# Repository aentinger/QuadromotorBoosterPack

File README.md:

💾 Quadromotor BoosterPack
==========================

# 📸 Image

# 📂 Description

The Quadromotor BoosterPack in combination with a MSP430 Launchpad facilitates the control of a 1, 2 or 4 DC motors, or alternatively  of 2 stepper motors. Additionally, outputs of the motor drivers can be connected in parallel. Therefor, two motors with an maximum output current of 2 A can be controlled, or one motor with an maximum output current of 4 A. For a quick and easy start a sample Code Composer Studio project (written in programming language C) is available.

**Features**

* Control of 1, 2 or 4 DC motors OR 
* Control of 2 stepper motors
* Speed and rotational direction adjustable
* Supply voltage range: 4 V to 16 V
* Output current per motor for 4/2/1 motors: 1 A / 2 A / 4 A
* To be used with MSP430 Launchpad
* Sample projects available for Code Composer Studio

# 🎥 [Video](images/quadromotor_booster_pack_demo.mp4)

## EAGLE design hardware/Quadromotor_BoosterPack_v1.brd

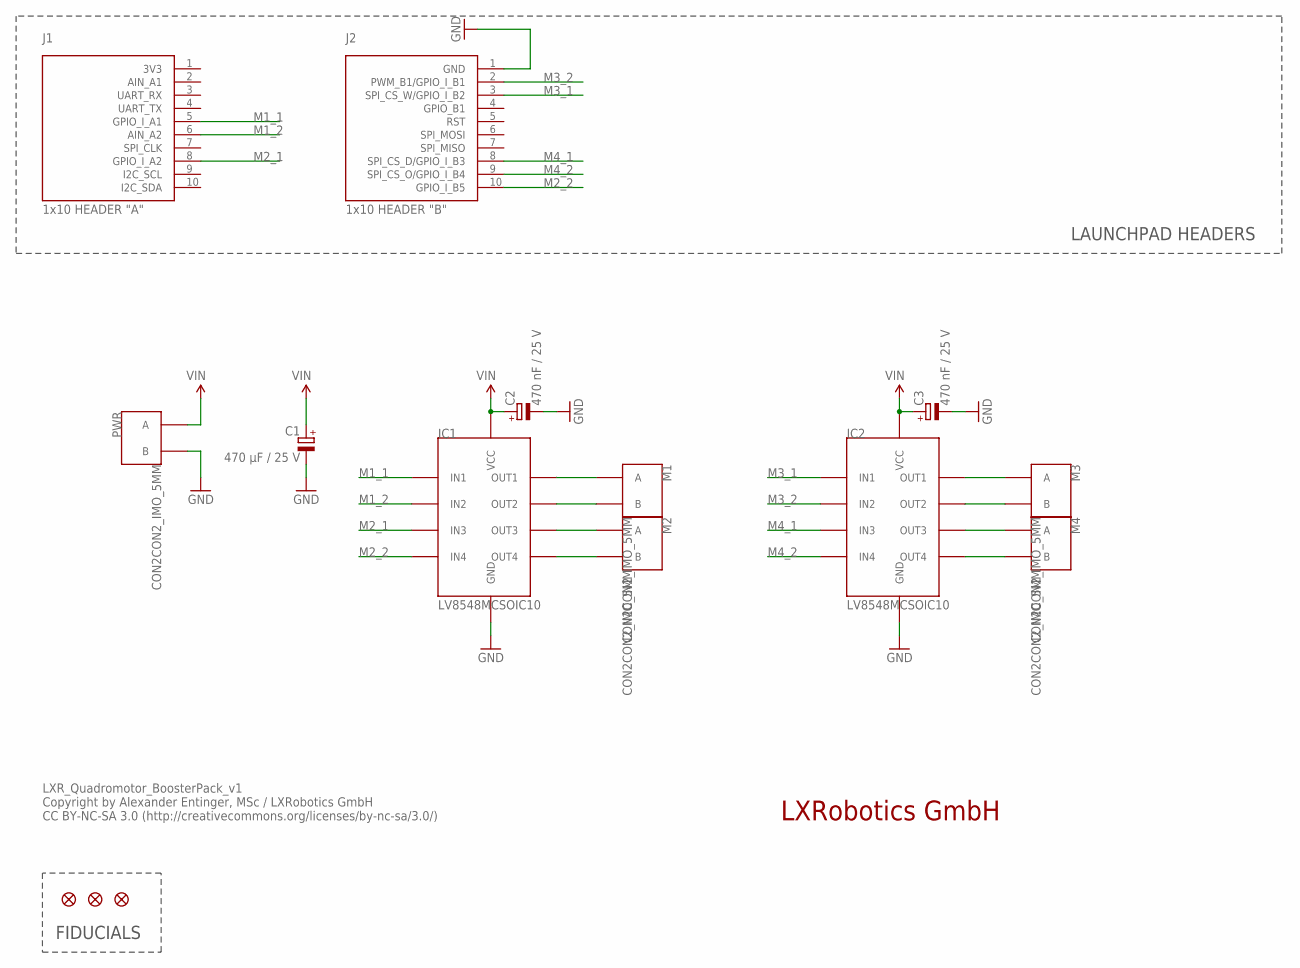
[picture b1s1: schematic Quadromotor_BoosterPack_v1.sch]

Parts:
C1: 470 µF / 25 V; E5-10,5
C2, C3: 470 nF / 25 V; KEMET_A
FID1, FID2, FID3: FIDUCIAL; FIDUCIAL_L10
IC1, IC2: LV8548MCSOIC10; SOIC10
J1: 1x10 HEADER "A"; 1X10
J2: 1x10 HEADER "B"; 1X10
M1, M2, M3, M4: CON2CON2_IMO_5MM; CON2_IMO
PWR: CON2CON2_IMO_5MM; CON2_IMO

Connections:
GND: C1.-, C2.CATHODE (-), C3.CATHODE (-), IC1.6 (GND), IC2.6 (GND), J2.1 (GND), PWR.P$2 (B)
M1_1: IC1.2 (IN1), J1.5 (GPIO_I_A1)
M1_2: IC1.3 (IN2), J1.6 (AIN_A2)
M2_1: IC1.4 (IN3), J1.8 (GPIO_I_A2)
M2_2: IC1.5 (IN4), J2.10 (GPIO_I_B5)
M3_1: IC2.2 (IN1), J2.3 (SPI_CS_W/GPIO_I_B2)
M3_2: IC2.3 (IN2), J2.2 (PWM_B1/GPIO_I_B1)
M4_1: IC2.4 (IN3), J2.8 (SPI_CS_D/GPIO_I_B3)
M4_2: IC2.5 (IN4), J2.9 (SPI_CS_O/GPIO_I_B4)
unnamed: IC1.10 (OUT1), M1.P$1 (A)
unnamed: IC1.9 (OUT2), M1.P$2 (B)
unnamed: IC1.8 (OUT3), M2.P$1 (A)
unnamed: IC1.7 (OUT4), M2.P$2 (B)
unnamed: IC2.10 (OUT1), M3.P$1 (A)
unnamed: IC2.9 (OUT2), M3.P$2 (B)
unnamed: IC2.8 (OUT3), M4.P$1 (A)
unnamed: IC2.7 (OUT4), M4.P$2 (B)
VIN: C1.+, C2.ANODE (+), C3.ANODE (+), IC1.1 (VCC), IC2.1 (VCC), PWR.P$1 (A)

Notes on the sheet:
LAUNCHPAD HEADERS
FIDUCIALS
LXRobotics GmbH
LXR_Quadromotor_BoosterPack_v1 Copyright by Alexander Entinger, MSc / LXRobotics GmbH CC BY-NC-SA 3.0 (http://creativecommons.org/licenses/by-nc-sa/3.0/)

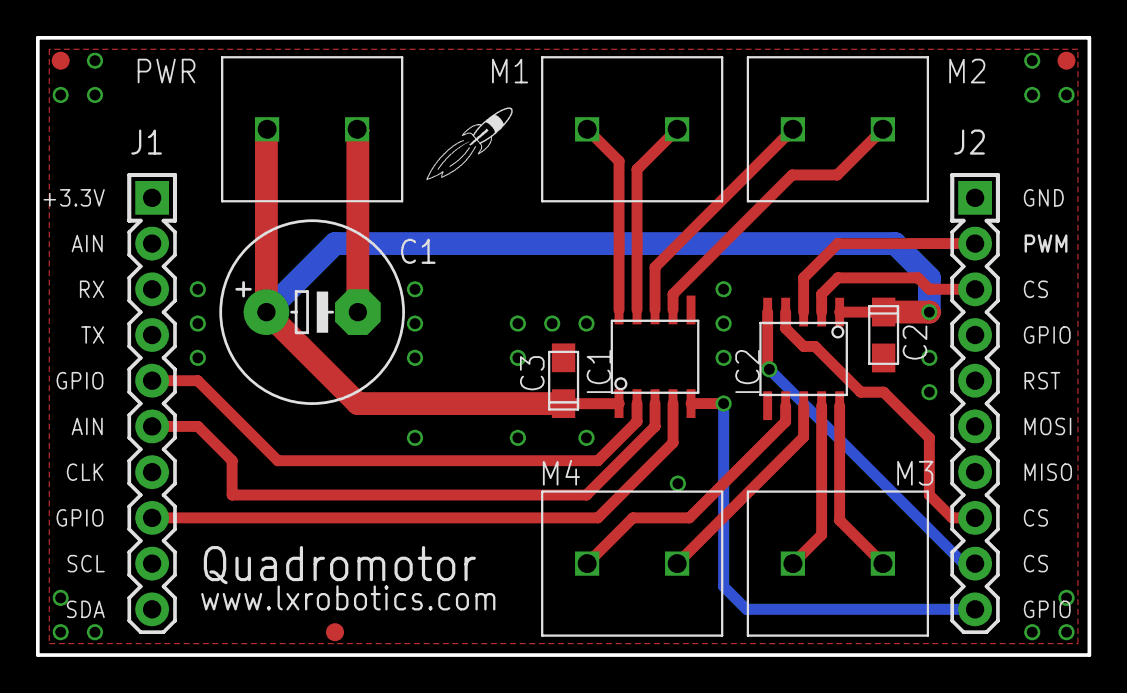
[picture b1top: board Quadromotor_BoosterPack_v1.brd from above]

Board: 2 copper layers, 58.4 x 34.3 mm, 16 parts (0 on the bottom side), 18 nets.

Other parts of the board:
U$1: LOGO-ROCKET

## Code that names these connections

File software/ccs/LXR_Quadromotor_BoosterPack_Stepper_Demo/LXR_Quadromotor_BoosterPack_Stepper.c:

/**
 * @author Alexander Entinger, MSc / LXRobotics
 * @brief this file contains the code how to control a stepper motor with the LXRobotics quadromotor booster pack
 * @file LXR_Quadromotor_BoosterPack_Stepper.c
 * @license CC BY-NC-SA 3.0 ( http://creativecommons.org/licenses/by-nc-sa/3.0/ )
 */

#include "LXR_Quadromotor_BoosterPack_Stepper.h"
#include <msp430.h>

/* DEFINES */
#define M1_1_DIR		(P1DIR)
#define M1_2_DIR		(P1DIR)
#define M1_1_OUT		(P1OUT)
#define M1_2_OUT		(P1OUT)
#define M1_1			(1<<3)
#define M1_2			(1<<4)

#define M2_1_DIR		(P2DIR)
#define M2_2_DIR		(P2DIR)
#define M2_1_OUT		(P2OUT)
#define M2_2_OUT		(P2OUT)
#define M2_1			(1<<0)
#define M2_2			(1<<3)

#define M3_1_DIR		(P2DIR)
#define M3_2_DIR		(P2DIR)
#define M3_1_OUT		(P2OUT)
#define M3_2_OUT		(P2OUT)
#define M3_1			(1<<7)
#define M3_2			(1<<6)

#define M4_1_DIR		(P2DIR)
#define M4_2_DIR		(P2DIR)
#define M4_1_OUT		(P2OUT)
#define M4_2_OUT		(P2OUT)
#define M4_1			(1<<5)
#define M4_2			(1<<4)

/* MACROS */
#define M1_1_HIGH		M1_1_OUT |= M1_1
#define M1_1_LOW		M1_1_OUT &= ~M1_1
#define M1_2_HIGH		M1_2_OUT |= M1_2
#define M1_2_LOW		M1_2_OUT &= ~M1_2

#define M2_1_HIGH		M2_1_OUT |= M2_1
#define M2_1_LOW		M2_1_OUT &= ~M2_1
#define M2_2_HIGH		M2_2_OUT |= M2_2
#define M2_2_LOW		M2_2_OUT &= ~M2_2

#define M3_1_HIGH		M3_1_OUT |= M3_1
#define M3_1_LOW		M3_1_OUT &= ~M3_1
#define M3_2_HIGH		M3_2_OUT |= M3_2
#define M3_2_LOW		M3_2_OUT &= ~M3_2

#define M4_1_HIGH		M4_1_OUT |= M4_1
#define M4_1_LOW		M4_1_OUT &= ~M4_1
#define M4_2_HIGH		M4_2_OUT |= M4_2
#define M4_2_LOW		M4_2_OUT &= ~M4_2

/* CONSTANTS */
static uint8_t const NUMBER_OF_STEPS = 4;

/* DATA TYPES */
typedef struct {
	uint8_t current_step;
} s_stepper_params;

/* DATA */
static volatile s_stepper_params m_motor_1_params = {0};
static volatile s_stepper_params m_motor_2_params = {0};

/* PROTOTYPES */
void motor_1_step(uint8_t const step);
void motor_2_step(uint8_t const step);

/* GLOBAL FUNCTIONS */

/**
 * @brief initializes the booster pack
 */
void init_quadromotor_booster_pack_stepper()  {
	// set all gpios to outputs and low
	M1_1_DIR |= M1_1;	M1_1_LOW;
	M1_2_DIR |= M1_2;	M1_2_LOW;
	M2_1_DIR |= M2_1;	M2_1_LOW;
	M2_2_DIR |= M2_2;	M2_2_LOW;
	M3_1_DIR |= M3_1;	M3_1_LOW;
	M3_2_DIR |= M3_2;	M3_2_LOW;
	M4_1_DIR |= M4_1;	M4_1_LOW;
	M4_2_DIR |= M4_2;	M4_2_LOW;

	// disable all secondary port functions
	P1SEL = 0x00; P1SEL2 = 0x00;
	P2SEL = 0x00; P2SEL2 = 0x00;
}

/**
 * @brief steps the motor one step forward or one step backwards
 */
void motor_1_do_one_step(E_DIRECTION const dir) {
	if(dir == FWD) {
		(m_motor_1_params.current_step == (NUMBER_OF_STEPS-1)) ? m_motor_1_params.current_step = 0 : m_motor_1_params.current_step++;
	} else if(dir == BWD) {
		(m_motor_1_params.current_step == 0) ? m_motor_1_params.current_step = (NUMBER_OF_STEPS-1) : m_motor_1_params.current_step--;
	}
	motor_1_step(m_motor_1_params.current_step);
}

/**
 * @brief steps the motor one step forward or one step backwards
 */
void motor_2_do_one_step(E_DIRECTION const dir) {
	if(dir == FWD) {
		(m_motor_2_params.current_step == (NUMBER_OF_STEPS-1)) ? m_motor_2_params.current_step = 0 : m_motor_2_params.current_step++;
	} else if(dir == BWD) {
		(m_motor_2_params.current_step == 0) ? m_motor_2_params.current_step = (NUMBER_OF_STEPS-1) : m_motor_2_params.current_step--;
	}
	motor_2_step(m_motor_2_params.current_step);
}

/* LOCAL FUNCTIONS */

// M1+ = Coil 1A
// M1- = Coil 1B
// M2+ = Coil 2A
// M2- = Coil 2B

/**
 * @brief steps the motor to step number step
 */
void motor_1_step(uint8_t const step) {
	switch(step) {
	case 0: {
		M1_1_HIGH;
		M1_2_LOW;
		M2_1_HIGH;
		M2_2_LOW;
	} break;
	case 1: {
		M1_1_HIGH;
		M1_2_LOW;
		M2_1_LOW;
		M2_2_HIGH;
	} break;
	case 2: {
		M1_1_LOW;
		M1_2_HIGH;
		M2_1_LOW;
		M2_2_HIGH;
	} break;
	case 3: {
		M1_1_LOW;
		M1_2_HIGH;
		M2_1_HIGH;
		M2_2_LOW;
	} break;
	default: break;
	}
}

// M3+ = Coil 1A
// M3- = Coil 1B
// M4+ = Coil 2A
// M4- = Coil 2B

/**
 * @brief steps the motor to step number step
 */
void motor_2_step(uint8_t const step) {
	switch(step) {
	case 0: {
		M3_1_HIGH;
		M3_2_LOW;
		M4_1_HIGH;
		M4_2_LOW;
	} break;
	case 1: {
		M3_1_HIGH;
		M3_2_LOW;
		M4_1_LOW;
		M4_2_HIGH;
	} break;
	case 2: {
		M3_1_LOW;
		M3_2_HIGH;
		M4_1_LOW;
		M4_2_HIGH;
	} break;
	case 3: {
		M3_1_LOW;
		M3_2_HIGH;
		M4_1_HIGH;
		M4_2_LOW;
	} break;
	default: break;
	}
}

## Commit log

2014-02-06 initial checkin of files
2014-02-09 added stepper demo software
2015-09-09 adding quadromotor energia library
2015-09-09 adding working version of energia library
2017-06-27 Adding hardware + images
2025-03-26 Upload demo video.
2025-03-26 Upload BOM.
2025-03-26 Pretty up README.

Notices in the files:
README.md:
License: CC BY-NC-SA 4.0
parts and their libraries:
SparkFun-Aesthetics: Licensing: CC v3.0 Share-Alike You are welcome to use this library for commercial purposes.
